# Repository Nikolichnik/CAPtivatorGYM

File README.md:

# CAPtivatorGYM

<h4>Supercapacitor testing device.</h4> 

It is designed to automate process of charging/discharging supercapacitors while capturing, displaying and transmitting all relevant data both locally and through USB connection. Capable of independent operation as well as in conjuction with companion desktop software - <a href="https://github.com/Nikolichnik/CAPtivatorINTEL"><em>CAPtivatorINTEL</em></a>.

<hr>

<p align="center">
  
</p>

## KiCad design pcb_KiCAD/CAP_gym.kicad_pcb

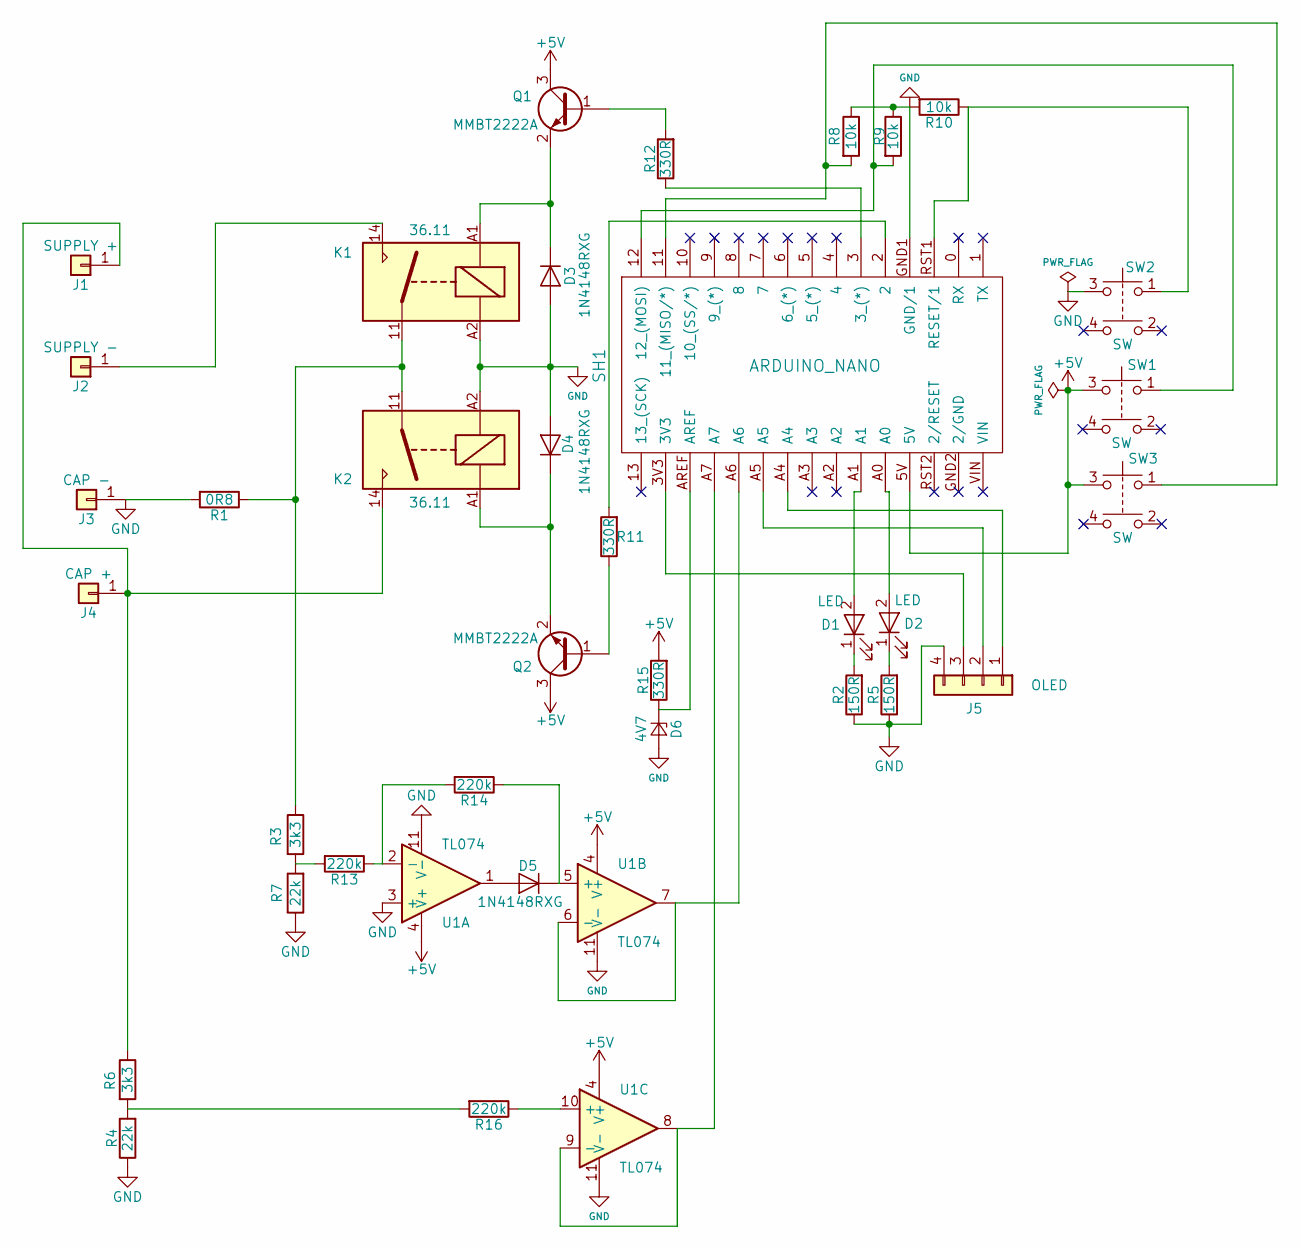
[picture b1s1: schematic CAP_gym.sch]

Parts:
D1, D2: LED; LED_D3.0mm
D3, D4, D5: 1N4148RXG; D_1206
D6: 4V7; D_MiniMELF
J1: SUPPLY +; Pin_Header_Straight_1x01_Pitch2.54mm
J2: SUPPLY -; Pin_Header_Straight_1x01_Pitch2.54mm
J3: CAP -; Pin_Header_Straight_1x01_Pitch2.54mm
J4: CAP +; Pin_Header_Straight_1x01_Pitch2.54mm
J5: OLED; Pin_Header_Straight_1x04_Pitch2.54mm
K1, K2: 36.11; Relay_SPDT_Finder_36.11
Q1, Q2: MMBT2222A; SOT-23
R1: 0R8; R_Axial_Power_L50.0mm_W9.0mm_P55.88mm
R2, R5: 150R; R_0805
R3, R6: 3k3; R_0805
R4, R7: 22k; R_0805
R8, R9, R10: 10k; R_0805
R11, R12, R15: 330R; R_0805
R13, R14, R16: 220k; R_0805
SH1: ARDUINO_NANO; ARDUINO_NANO_2_CONTOUR_ELL
SW1, SW2, SW3: SW; SW_TH_Tactile_Omron_B3F-10xx
U1: TL074; SO14

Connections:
+5V: Q1.3 (C), Q2.3 (C), R15.2, SH1.5V, SW1.3, SW3.3, U1.4 (V+)
GND: D3.2 (A), D4.2 (A), D6.2 (A), J3.1, J5.4, K1.A2, K2.A2, R1.2, R2.1, R4.1, R5.1, R7.1, R8.1, R9.1, R10.2, SH1.GND1 (GND/1), SW2.3, U1.3 (+), U1.11 (V-)
unnamed: D1.1 (K), R2.2
unnamed: D1.2 (A), SH1.A1
unnamed: D2.1 (K), R5.2
unnamed: D2.2 (A), SH1.A0
unnamed: D3.1 (K), K1.A1, Q1.2 (E)
unnamed: D4.1 (K), K2.A1, Q2.2 (E)
unnamed: D5.1 (K), R14.1, U1.5 (+)
unnamed: D5.2 (A), U1.1
unnamed: D6.1 (K), R15.1, SH1.AREF
unnamed: J1.1, J4.1, K2.14, R6.1
unnamed: J2.1, K1.14
unnamed: J5.1, SH1.A4
unnamed: J5.2, SH1.A5
unnamed: J5.3, SH1.3V3
unnamed: K1.11, K2.11, R1.1, R3.1
unnamed: Q1.1 (B), R12.2
unnamed: Q2.1 (B), R11.1
unnamed: R8.2, SH1.11 (11_(MISO/*)), SW3.1
unnamed: R9.2, SH1.12 (12_(MOSI)), SW1.1
unnamed: R10.1, SH1.RST1 (RESET/1), SW2.1
unnamed: R11.2, SH1.2
unnamed: R12.1, SH1.3 (3_(*))
unnamed: R13.1, R14.2, U1.2 (-)
unnamed: R3.2, R7.2, R13.2
unnamed: R16.1, U1.10 (+)
unnamed: R4.2, R6.2, R16.2
unnamed: SH1.A6, U1.6 (-), U1.7
unnamed: SH1.A7, U1.8, U1.9 (-)

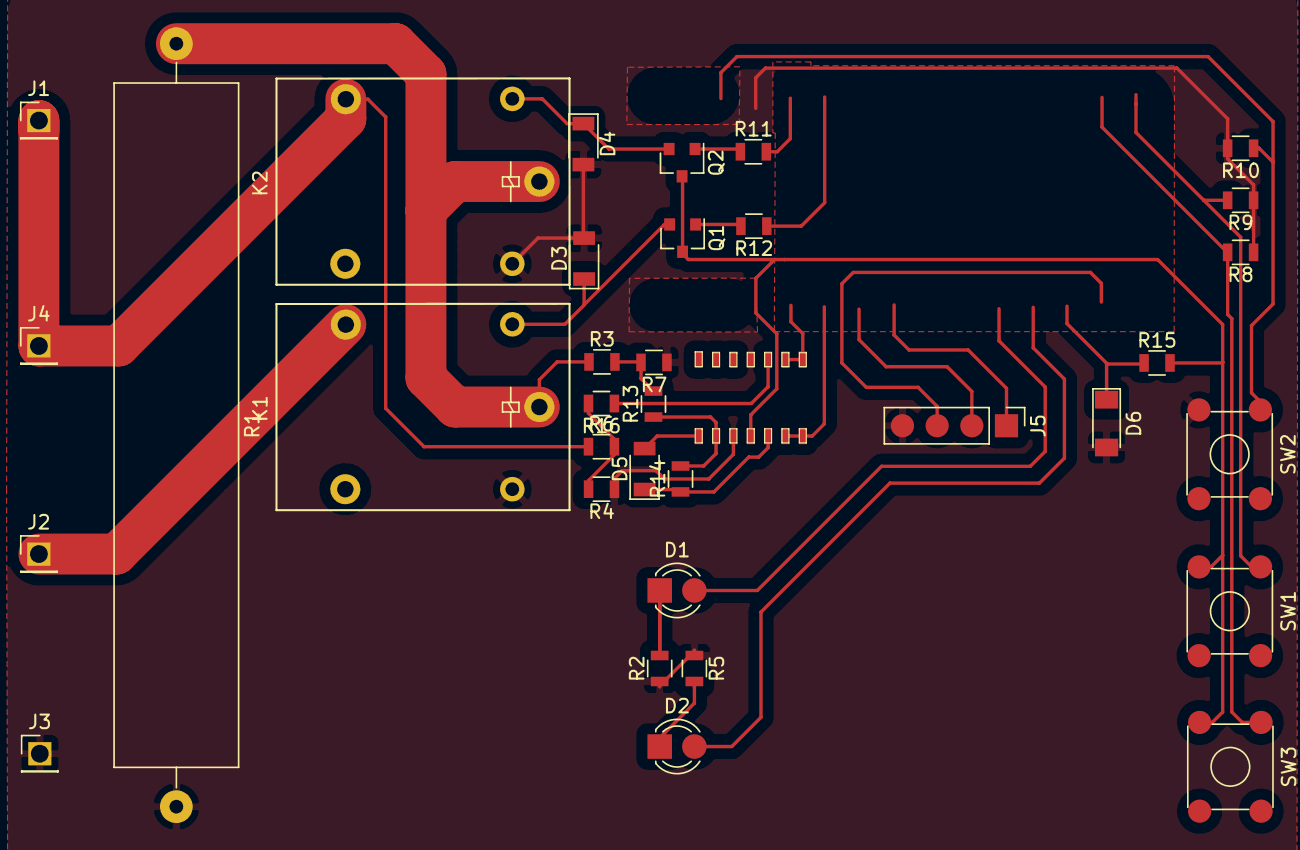
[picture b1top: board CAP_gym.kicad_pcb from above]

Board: 2 copper layers, 36 parts (1 on the bottom side), 30 nets.

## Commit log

2025-08-27 Update image link and attributes in README
